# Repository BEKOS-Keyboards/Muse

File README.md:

# Muse
BOSS Keyboards Muse CAD and Design files

This is a full size "104" key keyboard that will run the QMK firmware, it has extra keys above the number row to allow for media control or other macros to be bound to the keys

Shield: [![CC BY-SA 4.0][cc-by-sa-shield]][cc-by-sa]

This work is licensed under a
[Creative Commons Attribution-ShareAlike 4.0 International License][cc-by-sa].

[![CC BY-SA 4.0][cc-by-sa-image]][cc-by-sa]

[cc-by-sa]: http://creativecommons.org/licenses/by-sa/4.0/
[cc-by-sa-image]: https://licensebuttons.net/l/by-sa/4.0/88x31.png
[cc-by-sa-shield]: https://img.shields.io/badge/License-CC%20BY--SA%204.0-lightgrey.svg

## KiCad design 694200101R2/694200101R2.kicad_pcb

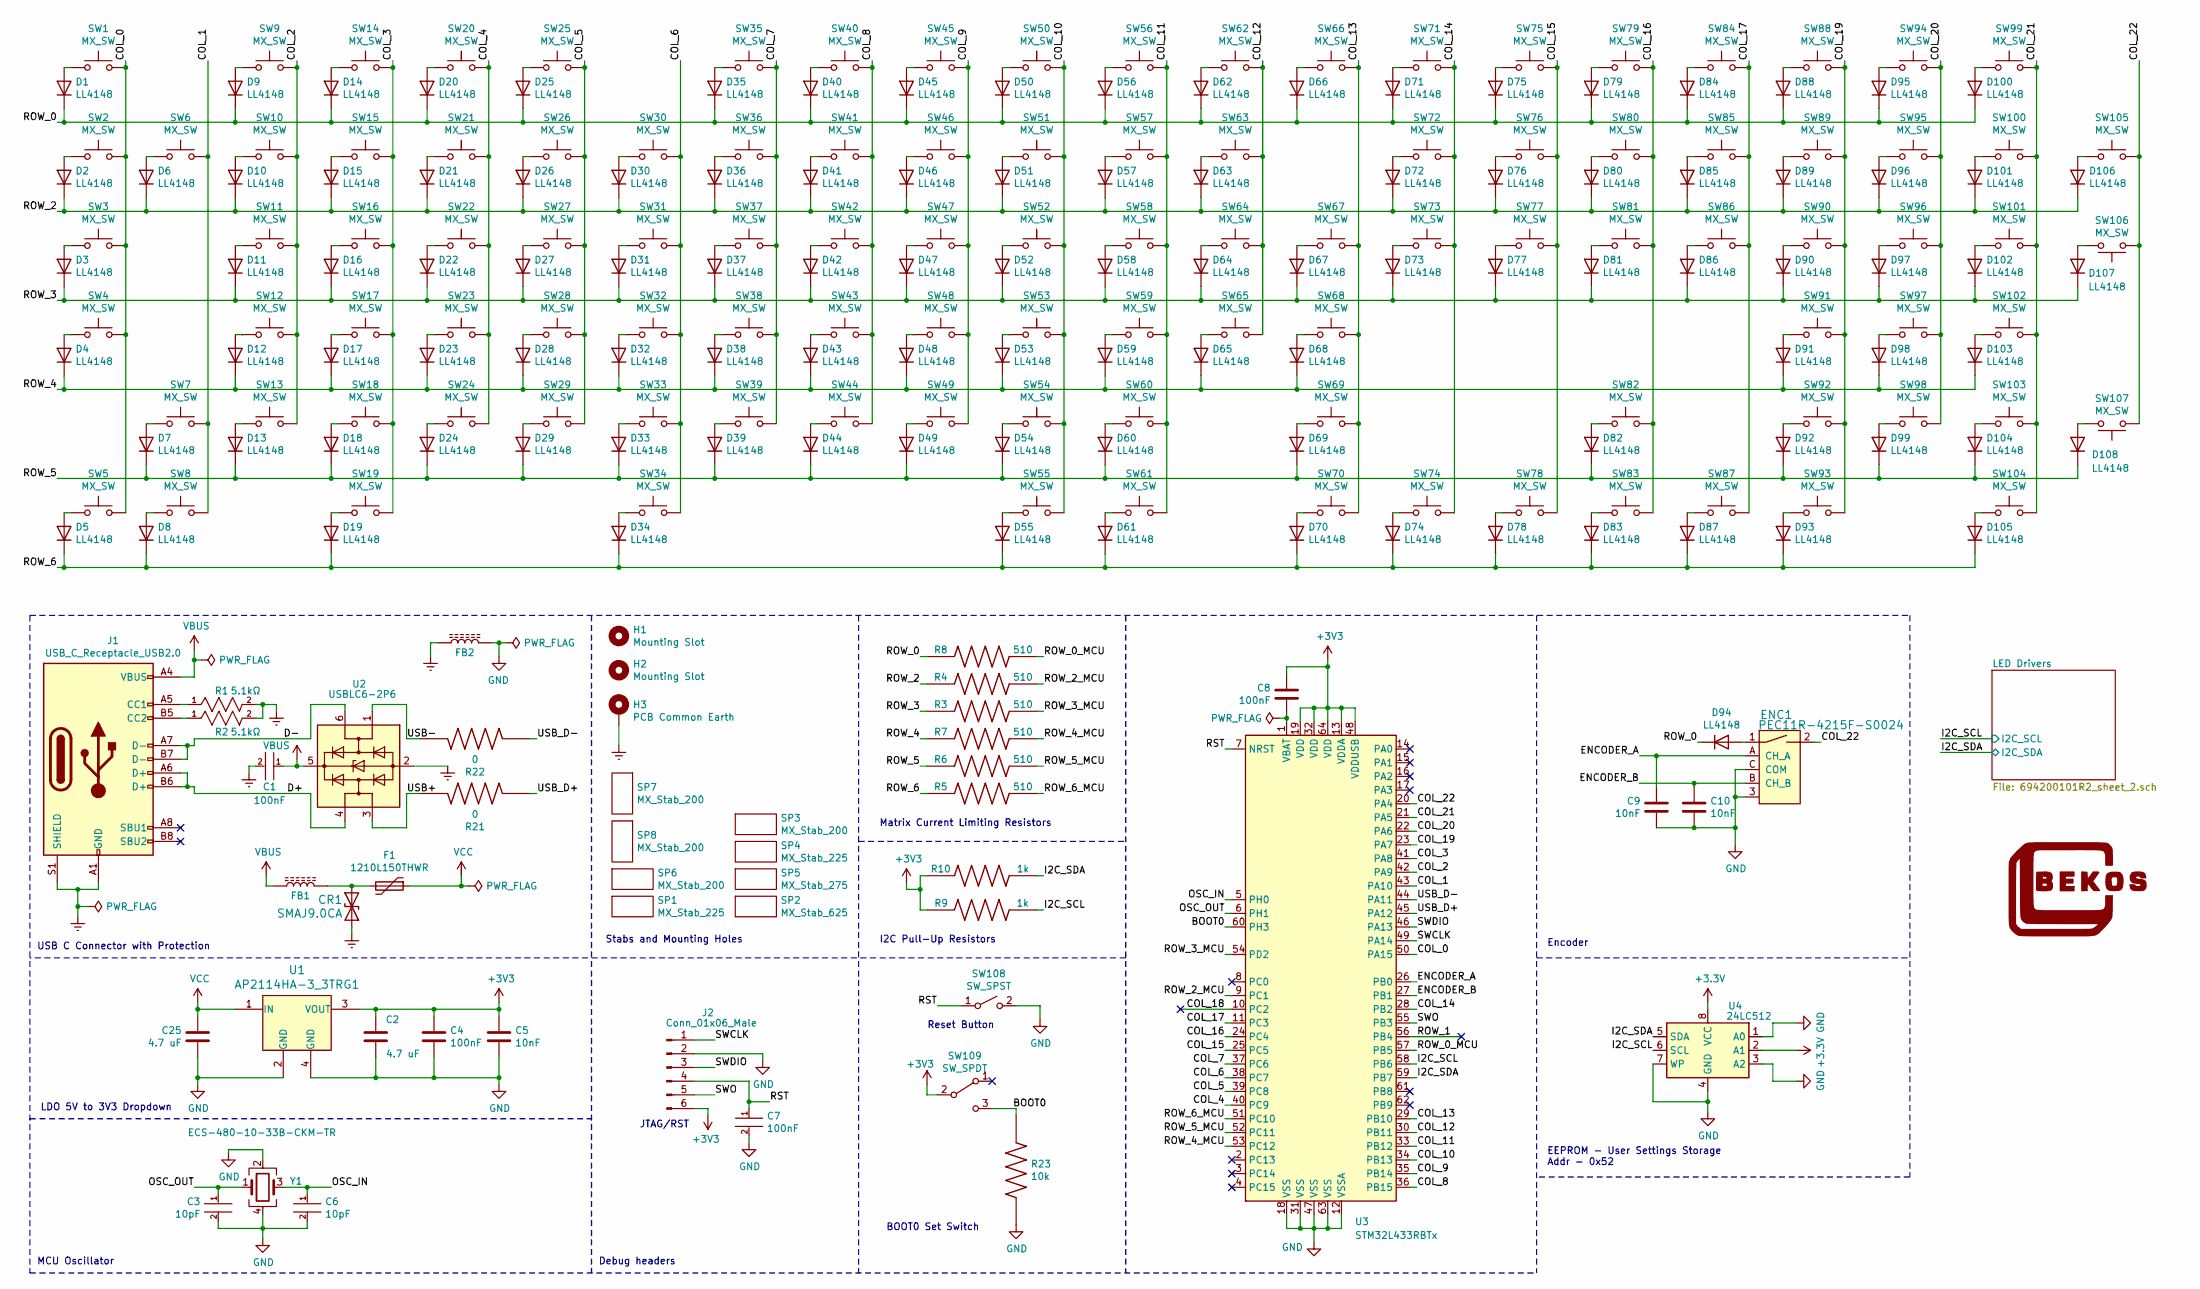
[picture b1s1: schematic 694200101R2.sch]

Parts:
C1, C7: CL10B104KB8NNNL; C_0603_1608Metric; tolerance 10%; voltage rating 50V
C2, C25: 4.7 uF; C_0805_2012Metric
C3, C6: 06035A100JAT2A; C_0603_1608Metric; tolerance 5%; voltage rating 50V; mouser part number 581-06035A100J; digikey description CAP CER 10PF 50V C0G/NP0 0603
C4, C8: 100nF; C_0603_1608Metric
C5, C9, C10: 10nF; C_0603_1608Metric
CR1: SMAJ9.0CA
D1, D9, D14, D20, D25, D35, D40, D45, D50, D56, D62, D66, D71, D75, D79: LL4148; D_MiniMELF
D2, D3, D4, D5, D6, D7, D8, D10, D11, D12, D13, D15, D16, D17, D18, D19, D21, D22, D23, D24, D26, D27, D28, D29, D30, D31, D32, D33, D34, D36, D37, D38, D39, D41, D42, D43, D44, D46, D47, D48, D49, D51, D52, D53, D54, D55, D57, D58, D59, D60, D61, D63, D64, D65, D67, D68, D69, D70, D72, D73, D74, D76, D77, D78, D80, D81, D82, D83, D84, D85, D86, D87, D88, D89, D90, D91, D92, D93, D94, D95, D96, D97, D98, D99, D100, D101, D102, D103, D104, D105, D106, D107, D108: LL4148; D_MiniMELF; mouser part number 512-LL4148; digikey description DIODE GEN PURP 100V 200MA SOD80
ENC1: PEC11R-4215F-S0024; Rotary_Encoder_Switched_PEC11R; MPN PEC11R-4215F-S0024; Digi-Key_PN PEC11R-4215F-S0024-ND
F1: 1210L150THWR; Fuse_1210_3225Metric_Castellated
FB1, FB2: FBMJ3216HM600-T; L_1206_3216Metric
H1, H2: Mounting Slot; MountingHole_M2_edge
H3: PCB Common Earth; MountingHole_3.5mm_Pad_TopBottom
J1: USB_C_Receptacle_USB2.0; USB_C_Receptacle_GCT_USB4085
J2: Conn_01x06_Male; PinHeader_1x06_P2.54mm_Vertical
R1, R2: RC0603FR-075K1L; R_0603_1608Metric; power rating 0.1W; tolerance 1%; mouser part number 603-RC0603FR-075K1L; digikey description RES SMD 5.1K OHM 1% 1/10W 0603
R3, R4, R5, R6, R7, R8: RMCF0805FT510R; R_0805_2012Metric
R9, R10: RMCF0603FT1K00; R_0603_1608Metric
R21, R22: MCT06030Z0000ZP500; R_0603_1608Metric
R23: RNCP0603FTD10K0; R_0603_1608Metric
SP1, SP4: MX_Stab_225; Mx_Stab_225
SP2: MX_Stab_625; Mx_Stab_625
SP3, SP6, SP7, SP8: MX_Stab_200; Mx_Stab_200
SP5: MX_Stab_275; Mx_Stab_275
SW1, SW2, SW3, SW4, SW5, SW6, SW7, SW8, SW9, SW10, SW11, SW12, SW13, SW14, SW15, SW16, SW17, SW18, SW19, SW20, SW21, SW22, SW23, SW24, SW25, SW26, SW27, SW28, SW29, SW30, SW31, SW32, SW33, SW34, SW35, SW36, SW37, SW38, SW39, SW40, SW41, SW42, SW43, SW44, SW45, SW46, SW47, SW48, SW49, SW50, SW51, SW52, SW53, SW54, SW55, SW56, SW57, SW58, SW59, SW60, SW61, SW62, SW63, SW64, SW65, SW66, SW67, SW68, SW69, SW70, SW71, SW72, SW73, SW74, SW75, SW76, SW77, SW78, SW79, SW80, SW81, SW82, SW83, SW84, SW85, SW86, SW87, SW88, SW89, SW90, SW91, SW92, SW93, SW94, SW95, SW96, SW97, SW98, SW99, SW100, SW101, SW102, SW103, SW104, SW105, SW106, SW107: MX_SW; millmax-mxalps
SW108: SW_SPST; SW_SPST_TL3342
SW109: SW_SPDT; SW_SPDT_PCM12
U1: AP2114HA-3_3TRG1; SOT-223; MPN AP2114H-3.3TRG1; Digi-Key_PN AP2114H-3.3TRG1DICT-ND
U2: USBLC6-2P6; SOT-666
U3: STM32L433RBTx; LQFP-64_10x10mm_P0.5mm
U4: 24LC512; SOIC-8_3.9x4.9mm_P1.27mm
Y1: ECS-480-10-33B-CKM-TR; XTAL_ECS-480-10-33B-CKM-TR

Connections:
/BOOT0: R23.1, SW109.3 (C), U3.60 (PH3)
/COL_0: SW1.2, SW2.2, SW3.2, SW4.2, SW5.2, U3.50 (PA15)
/COL_1: SW6.2, SW7.2, SW8.2, U3.43 (PA10)
/COL_2: SW9.2, SW10.2, SW11.2, SW12.2, SW13.2, U3.42 (PA9)
/COL_3: SW14.2, SW15.2, SW16.2, SW17.2, SW18.2, SW19.2, U3.41 (PA8)
/COL_4: SW20.2, SW21.2, SW22.2, SW23.2, SW24.2, U3.40 (PC9)
/COL_5: SW25.2, SW26.2, SW27.2, SW28.2, SW29.2, U3.39 (PC8)
/COL_6: SW30.2, SW31.2, SW32.2, SW33.2, SW34.2, U3.38 (PC7)
/COL_7: SW35.2, SW36.2, SW37.2, SW38.2, SW39.2, U3.37 (PC6)
/COL_8: SW40.2, SW41.2, SW42.2, SW43.2, SW44.2, U3.36 (PB15)
/COL_9: SW45.2, SW46.2, SW47.2, SW48.2, SW49.2, U3.35 (PB14)
/COL_10: SW50.2, SW51.2, SW52.2, SW53.2, SW54.2, SW55.2, U3.34 (PB13)
/COL_11: SW56.2, SW57.2, SW58.2, SW59.2, SW60.2, SW61.2, U3.33 (PB12)
/COL_12: SW62.2, SW63.2, SW64.2, SW65.2, U3.30 (PB11)
/COL_13: SW66.2, SW67.2, SW68.2, SW69.2, SW70.2, U3.29 (PB10)
/COL_14: SW71.2, SW72.2, SW73.2, SW74.2, U3.28 (PB2)
/COL_15: SW75.2, SW76.2, SW77.2, SW78.2, U3.25 (PC5)
/COL_16: SW79.2, SW80.2, SW81.2, SW82.2, SW83.2, U3.24 (PC4)
/COL_17: SW84.2, SW85.2, SW86.2, SW87.2, U3.11 (PC3)
/COL_18: U3.10 (PC2)
/COL_19: SW88.2, SW89.2, SW90.2, SW91.2, SW92.2, SW93.2, U3.23 (PA7)
/COL_20: SW94.2, SW95.2, SW96.2, SW97.2, SW98.2, U3.22 (PA6)
/COL_21: SW99.2, SW100.2, SW101.2, SW102.2, SW103.2, SW104.2, U3.21 (PA5)
/COL_22: ENC1.2, SW105.2, SW106.1, SW107.1, U3.20 (PA4)
/D+: J1.A6 (D+), J1.B6 (D+), U2.4 (I/O2)
/D-: J1.A7 (D-), J1.B7 (D-), U2.6 (I/O1)
/ENCODER_A: C9.1, ENC1.A (CH_A), U3.26 (PB0)
/ENCODER_B: C10.1, ENC1.B (CH_B), U3.27 (PB1)
/I2C_SCL: R9.2, U3.58 (PB6), U4.6 (SCL); also elsewhere on the board
/I2C_SDA: R10.2, U3.59 (PB7), U4.5 (SDA); also elsewhere on the board
/OSC_IN: C6.1, U3.5 (PH0), Y1.3
/OSC_OUT: C3.1, U3.6 (PH1), Y1.1
/ROW_0: D1.1 (K), D9.1 (K), D14.1 (K), D20.1 (K), D25.1 (K), D35.1 (K), D40.1 (K), D45.1 (K), D50.1 (K), D56.1 (K), D62.1 (K), D66.1 (K), D71.1 (K), D75.1 (K), D79.1 (K), D84.1 (K), D88.1 (K), D94.1 (K), D95.1 (K), D100.1 (K), R8.2
/ROW_0_MCU: R8.1, U3.57 (PB5)
/ROW_1: U3.56 (PB4)
/ROW_2: D2.1 (K), D6.1 (K), D10.1 (K), D15.1 (K), D21.1 (K), D26.1 (K), D30.1 (K), D36.1 (K), D41.1 (K), D46.1 (K), D51.1 (K), D57.1 (K), D63.1 (K), D72.1 (K), D76.1 (K), D80.1 (K), D85.1 (K), D89.1 (K), D96.1 (K), D101.1 (K), D106.1 (K), R4.1
/ROW_2_MCU: R4.2, U3.9 (PC1)
/ROW_3: D3.1 (K), D11.1 (K), D16.1 (K), D22.1 (K), D27.1 (K), D31.1 (K), D37.1 (K), D42.1 (K), D47.1 (K), D52.1 (K), D58.1 (K), D64.1 (K), D67.1 (K), D73.1 (K), D77.1 (K), D81.1 (K), D86.1 (K), D90.1 (K), D97.1 (K), D102.1 (K), D107.1 (K), R3.1
/ROW_3_MCU: R3.2, U3.54 (PD2)
/ROW_4: D4.1 (K), D12.1 (K), D17.1 (K), D23.1 (K), D28.1 (K), D32.1 (K), D38.1 (K), D43.1 (K), D48.1 (K), D53.1 (K), D59.1 (K), D65.1 (K), D68.1 (K), D91.1 (K), D98.1 (K), D103.1 (K), R7.1
/ROW_4_MCU: R7.2, U3.53 (PC12)
/ROW_5: D7.1 (K), D13.1 (K), D18.1 (K), D24.1 (K), D29.1 (K), D33.1 (K), D39.1 (K), D44.1 (K), D49.1 (K), D54.1 (K), D60.1 (K), D69.1 (K), D82.1 (K), D92.1 (K), D99.1 (K), D104.1 (K), D108.1 (K), R6.1
/ROW_5_MCU: R6.2, U3.52 (PC11)
/ROW_6: D5.1 (K), D8.1 (K), D19.1 (K), D34.1 (K), D55.1 (K), D61.1 (K), D70.1 (K), D74.1 (K), D78.1 (K), D83.1 (K), D87.1 (K), D93.1 (K), D105.1 (K), R5.1
/ROW_6_MCU: R5.2, U3.51 (PC10)
/RST: C7.1, J2.4, SW108.1 (A), U3.7 (NRST)
/SWCLK: J2.1, U3.49 (PA14)
/SWDIO: J2.3, U3.46 (PA13)
/SWO: J2.5, U3.55 (PB3)
/USB+: R21.1, U2.3 (I/O2)
/USB-: R22.1, U2.1 (I/O1)
/USB_D+: R21.2, U3.45 (PA12)
/USB_D-: R22.2, U3.44 (PA11)
Earth: C1.2, CR1.2 (A2), FB2.1, H3.1, J1.A1 (GND), J1.A12 (GND), J1.B1 (GND), J1.B12 (GND), J1.S1 (SHIELD), R1.2, R2.2, U2.2 (GND)
GND: C2.2, C3.2, C4.2, C5.2, C6.2, C7.2, C9.2, C10.2, C25.2, ENC1.3, ENC1.C (COM), FB2.2, J2.2, R23.2, SW108.2 (B), U1.2 (GND), U1.4 (GND), U3.12 (VSSA), U3.18 (VSS), U3.31 (VSS), U3.47 (VSS), U3.63 (VSS), U4.1 (A0), U4.3 (A2), U4.4 (GND), U4.7 (WP), Y1.2, Y1.4; also elsewhere on the board
unnamed: C8.2, U3.1 (VBAT)
unnamed: CR1.1 (A1), F1.2, FB1.1
unnamed: D1.2 (A), SW1.1
unnamed: D2.2 (A), SW2.1
unnamed: D3.2 (A), SW3.1
unnamed: D4.2 (A), SW4.1
unnamed: D5.2 (A), SW5.1
unnamed: D6.2 (A), SW6.1
unnamed: D7.2 (A), SW7.1
unnamed: D8.2 (A), SW8.1
unnamed: D9.2 (A), SW9.1
unnamed: D10.2 (A), SW10.1
unnamed: D11.2 (A), SW11.1
unnamed: D12.2 (A), SW12.1
unnamed: D13.2 (A), SW13.1
unnamed: D14.2 (A), SW14.1
unnamed: D15.2 (A), SW15.1
unnamed: D16.2 (A), SW16.1
unnamed: D17.2 (A), SW17.1
unnamed: D18.2 (A), SW18.1
unnamed: D19.2 (A), SW19.1
unnamed: D20.2 (A), SW20.1
unnamed: D21.2 (A), SW21.1
unnamed: D22.2 (A), SW22.1
unnamed: D23.2 (A), SW23.1
unnamed: D24.2 (A), SW24.1
unnamed: D25.2 (A), SW25.1
unnamed: D26.2 (A), SW26.1
unnamed: D27.2 (A), SW27.1
unnamed: D28.2 (A), SW28.1
unnamed: D29.2 (A), SW29.1
unnamed: D30.2 (A), SW30.1
unnamed: D31.2 (A), SW31.1
unnamed: D32.2 (A), SW32.1
unnamed: D33.2 (A), SW33.1
unnamed: D34.2 (A), SW34.1
unnamed: D35.2 (A), SW35.1
unnamed: D36.2 (A), SW36.1
unnamed: D37.2 (A), SW37.1
unnamed: D38.2 (A), SW38.1
unnamed: D39.2 (A), SW39.1
unnamed: D40.2 (A), SW40.1
unnamed: D41.2 (A), SW41.1
unnamed: D42.2 (A), SW42.1
unnamed: D43.2 (A), SW43.1
unnamed: D44.2 (A), SW44.1
unnamed: D45.2 (A), SW45.1
unnamed: D46.2 (A), SW46.1
unnamed: D47.2 (A), SW47.1
unnamed: D48.2 (A), SW48.1
unnamed: D49.2 (A), SW49.1
unnamed: D50.2 (A), SW50.1
unnamed: D51.2 (A), SW51.1
unnamed: D52.2 (A), SW52.1
unnamed: D53.2 (A), SW53.1
unnamed: D54.2 (A), SW54.1
unnamed: D55.2 (A), SW55.1
unnamed: D56.2 (A), SW56.1
unnamed: D57.2 (A), SW57.1
unnamed: D58.2 (A), SW58.1
unnamed: D59.2 (A), SW59.1
unnamed: D60.2 (A), SW60.1
unnamed: D61.2 (A), SW61.1
unnamed: D62.2 (A), SW62.1
unnamed: D63.2 (A), SW63.1
unnamed: D64.2 (A), SW64.1
unnamed: D65.2 (A), SW65.1
unnamed: D66.2 (A), SW66.1
unnamed: D67.2 (A), SW67.1
unnamed: D68.2 (A), SW68.1
unnamed: D69.2 (A), SW69.1
unnamed: D70.2 (A), SW70.1
unnamed: D71.2 (A), SW71.1
unnamed: D72.2 (A), SW72.1
unnamed: D73.2 (A), SW73.1
unnamed: D74.2 (A), SW74.1
unnamed: D75.2 (A), SW75.1
unnamed: D76.2 (A), SW76.1
unnamed: D77.2 (A), SW77.1
unnamed: D78.2 (A), SW78.1
unnamed: D79.2 (A), SW79.1
unnamed: D80.2 (A), SW80.1
unnamed: D81.2 (A), SW81.1
unnamed: D82.2 (A), SW82.1
unnamed: D83.2 (A), SW83.1
unnamed: D84.2 (A), SW84.1
unnamed: D85.2 (A), SW85.1
unnamed: D86.2 (A), SW86.1
unnamed: D87.2 (A), SW87.1
unnamed: D88.2 (A), SW88.1
unnamed: D89.2 (A), SW89.1
unnamed: D90.2 (A), SW90.1
unnamed: D91.2 (A), SW91.1
unnamed: D92.2 (A), SW92.1
unnamed: D93.2 (A), SW93.1
unnamed: D94.2 (A), ENC1.1
unnamed: D95.2 (A), SW94.1
unnamed: D96.2 (A), SW95.1
unnamed: D97.2 (A), SW96.1
unnamed: D98.2 (A), SW97.1
unnamed: D99.2 (A), SW98.1
unnamed: D100.2 (A), SW99.1
unnamed: D101.2 (A), SW100.1
unnamed: D102.2 (A), SW101.1
unnamed: D103.2 (A), SW102.1
unnamed: D104.2 (A), SW103.1
unnamed: D105.2 (A), SW104.1
unnamed: D106.2 (A), SW105.1
unnamed: D107.2 (A), SW106.2
unnamed: D108.2 (A), SW107.2
unnamed: J1.A5 (CC1), R1.1
unnamed: J1.B5 (CC2), R2.1
VBUS: C1.1, FB1.2, J1.A4 (VBUS), J1.A9 (VBUS), J1.B4 (VBUS), J1.B9 (VBUS), U2.5 (VBUS)
VCC: C25.1, F1.1, U1.1 (IN); also elsewhere on the board

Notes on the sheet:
USB C Connector with Protection
LDO 5V to 3V3 Dropdown
MCU Oscillator
JTAG/RST
Stabs and Mounting Holes
Matrix Current Limiting Resistors
I2C Pull-Up Resistors
Encoder
Debug headers
BOOT0 Set Switch
Reset Button
EEPROM - User Settings Storage Addr - 0x52

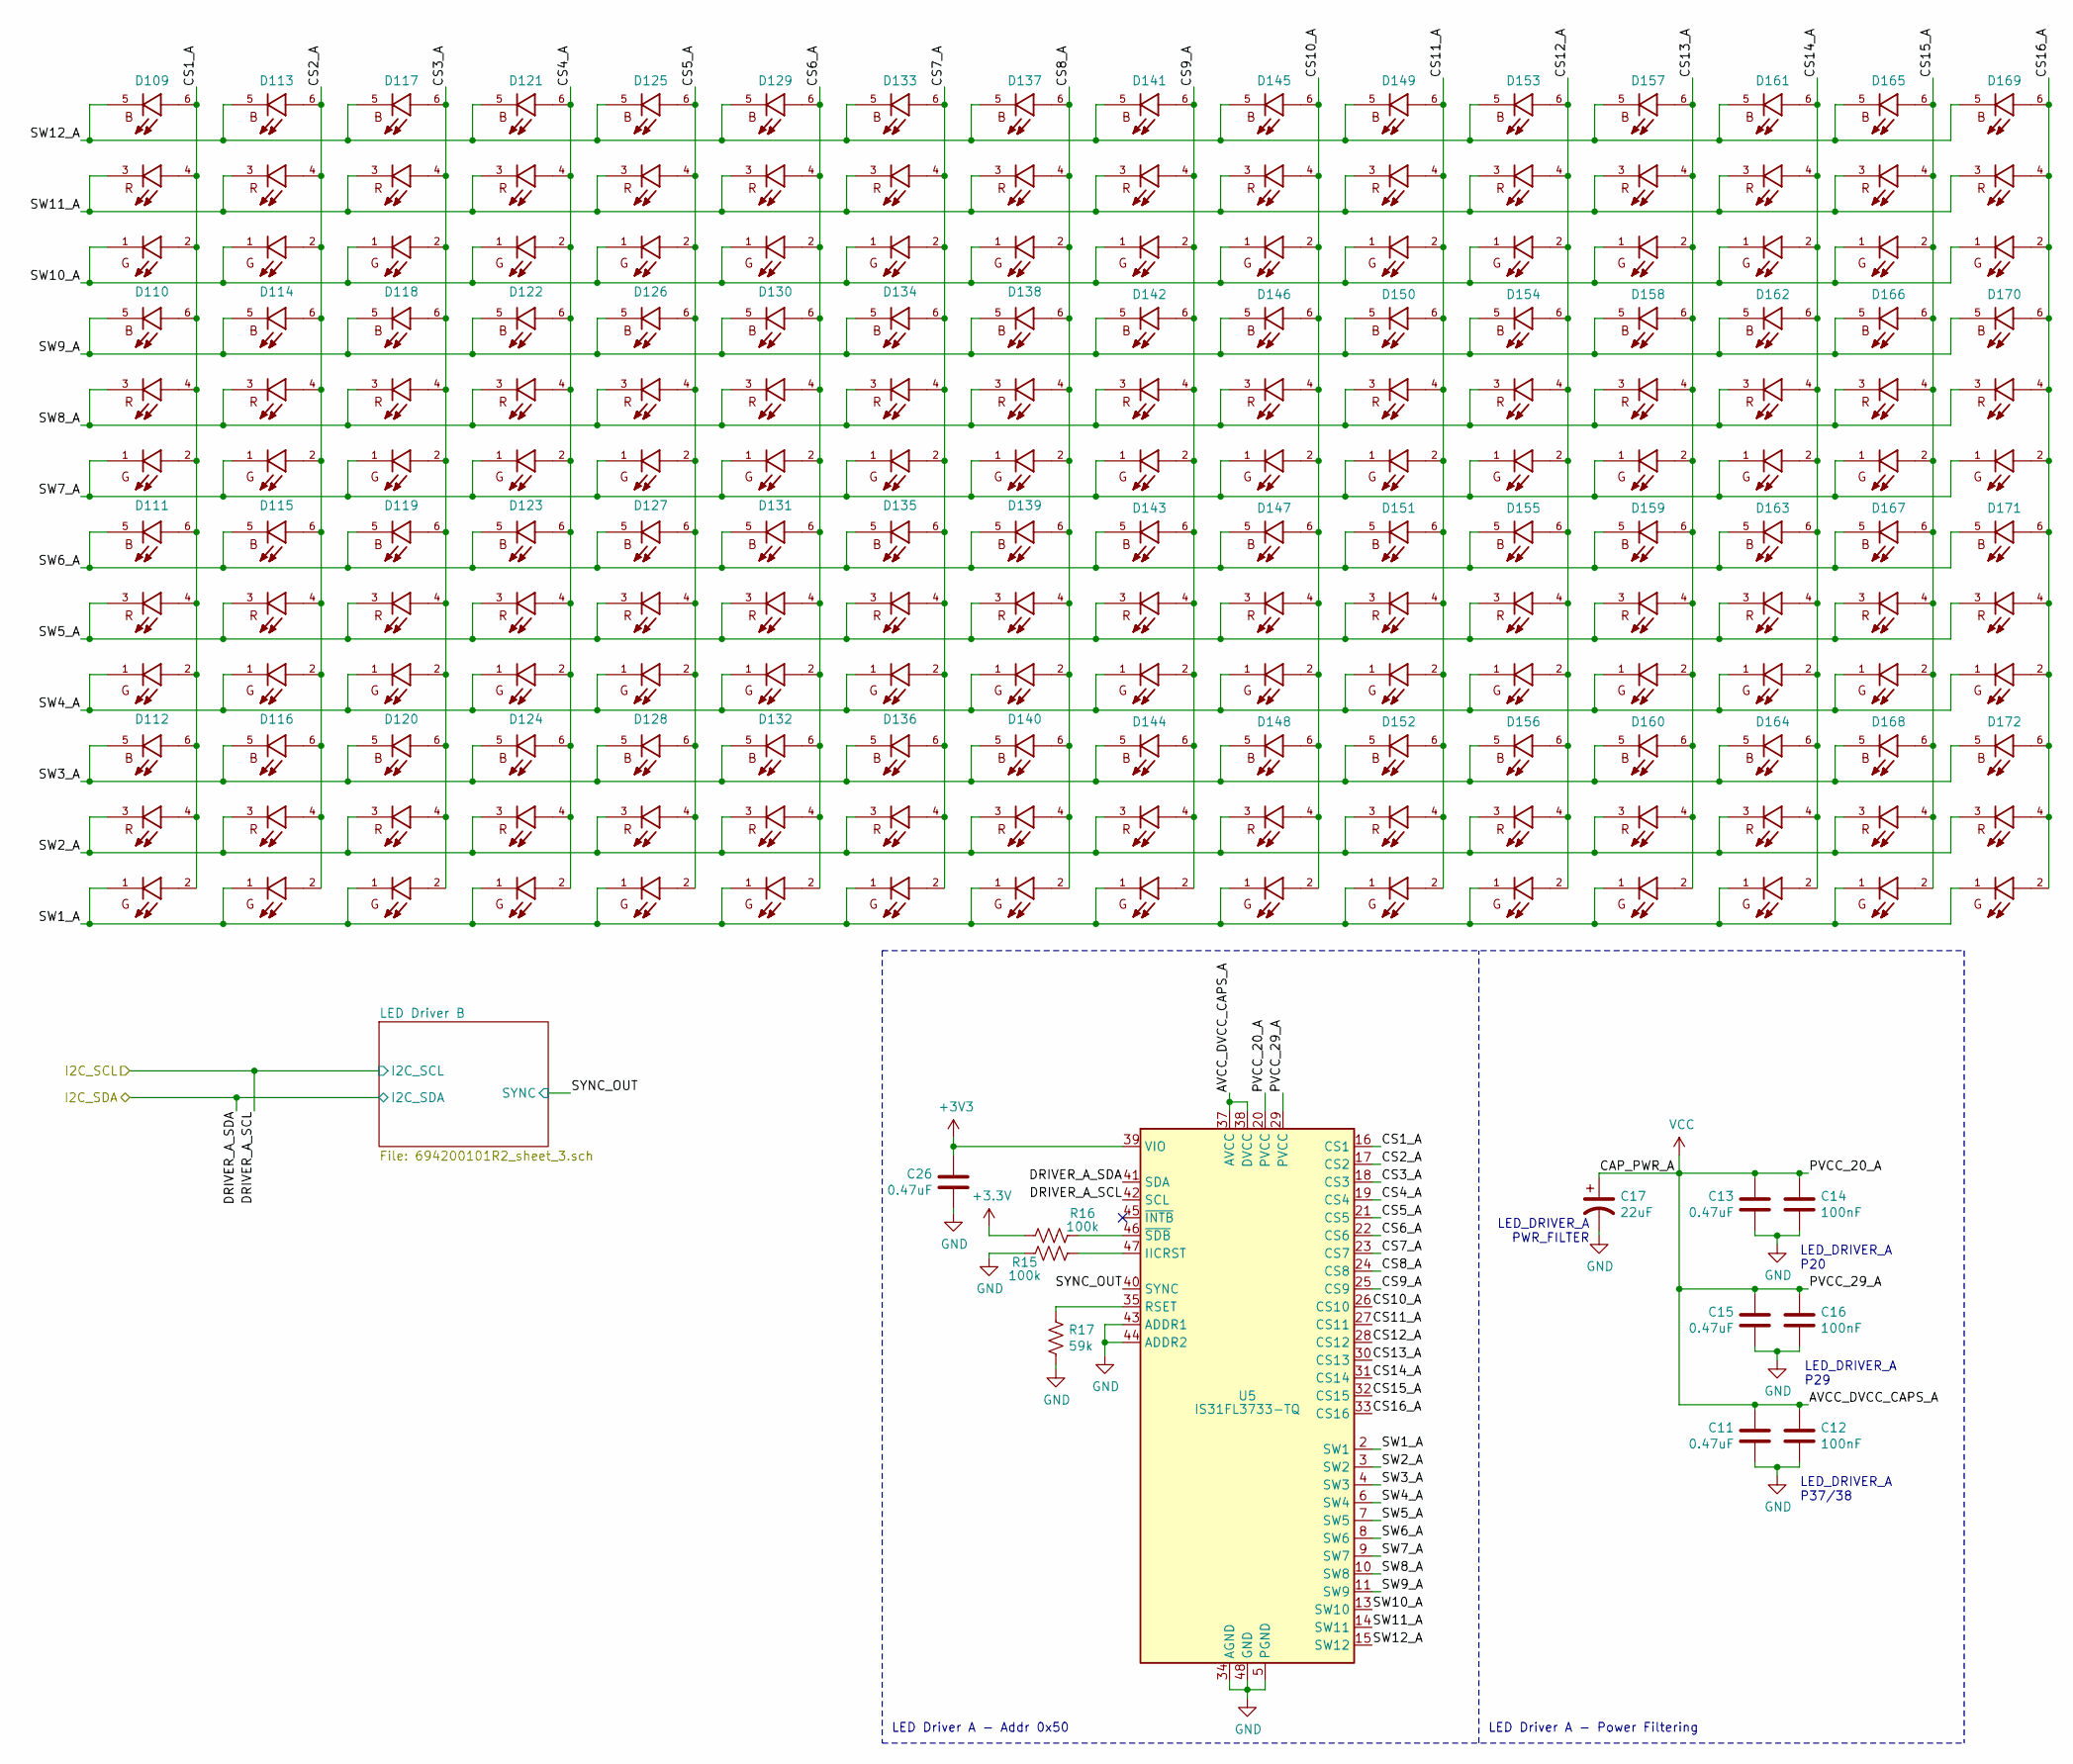
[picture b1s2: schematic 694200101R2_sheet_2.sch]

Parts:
C11, C13, C15, C26: 0.47uF; C_0603_1608Metric
C12, C14, C16: 100nF; C_0603_1608Metric
C17: 22uF; CP_EIA-3528-21_Kemet-B
D109, D110, D111, D112, D113, D114, D115, D116, D117, D118, D119, D120, D121, D122, D123, D124, D125, D126, D127, D128, D129, D130, D131, D132, D133, D134, D135, D136, D137, D138, D139, D140, D141, D142, D143, D144, D145, D146, D147, D148, D149, D150, D151, D152, D153, D154, D155, D156, D157, D158, D159, D160, D161, D162, D163, D164, D165, D166, D167, D168, D169, D170, D171, D172: 19-337C_RSBHGHC-A88_4T; 4T; PARTREV 2
R15, R16: 100k; R_0603_1608Metric
R17: 59k; R_2512_6332Metric
U5: IS31FL3733-TQ; TQFP-48-1EP_7x7mm_P0.5mm_EP5x5mm_ThermalVias

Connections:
/I2C_SCL: U5.42 (SCL); also elsewhere on the board
/I2C_SDA: U5.41 (SDA); also elsewhere on the board
/LED Drivers/CS1_A: D109.2, D109.4, D109.6, D110.2, D110.4, D110.6, D111.2, D111.4, D111.6, D112.2, D112.4, D112.6, U5.16 (CS1)
/LED Drivers/CS2_A: D113.2, D113.4, D113.6, D114.2, D114.4, D114.6, D115.2, D115.4, D115.6, D116.2, D116.4, D116.6, U5.17 (CS2)
/LED Drivers/CS3_A: D117.2, D117.4, D117.6, D118.2, D118.4, D118.6, D119.2, D119.4, D119.6, D120.2, D120.4, D120.6, U5.18 (CS3)
/LED Drivers/CS4_A: D121.2, D121.4, D121.6, D122.2, D122.4, D122.6, D123.2, D123.4, D123.6, D124.2, D124.4, D124.6, U5.19 (CS4)
/LED Drivers/CS5_A: D125.2, D125.4, D125.6, D126.2, D126.4, D126.6, D127.2, D127.4, D127.6, D128.2, D128.4, D128.6, U5.21 (CS5)
/LED Drivers/CS6_A: D129.2, D129.4, D129.6, D130.2, D130.4, D130.6, D131.2, D131.4, D131.6, D132.2, D132.4, D132.6, U5.22 (CS6)
/LED Drivers/CS7_A: D133.2, D133.4, D133.6, D134.2, D134.4, D134.6, D135.2, D135.4, D135.6, D136.2, D136.4, D136.6, U5.23 (CS7)
/LED Drivers/CS8_A: D137.2, D137.4, D137.6, D138.2, D138.4, D138.6, D139.2, D139.4, D139.6, D140.2, D140.4, D140.6, U5.24 (CS8)
/LED Drivers/CS9_A: D141.2, D141.4, D141.6, D142.2, D142.4, D142.6, D143.2, D143.4, D143.6, D144.2, D144.4, D144.6, U5.25 (CS9)
/LED Drivers/CS10_A: D145.2, D145.4, D145.6, D146.2, D146.4, D146.6, D147.2, D147.4, D147.6, D148.2, D148.4, D148.6, U5.26 (CS10)
/LED Drivers/CS11_A: D149.2, D149.4, D149.6, D150.2, D150.4, D150.6, D151.2, D151.4, D151.6, D152.2, D152.4, D152.6, U5.27 (CS11)
/LED Drivers/CS12_A: D153.2, D153.4, D153.6, D154.2, D154.4, D154.6, D155.2, D155.4, D155.6, D156.2, D156.4, D156.6, U5.28 (CS12)
/LED Drivers/CS13_A: D157.2, D157.4, D157.6, D158.2, D158.4, D158.6, D159.2, D159.4, D159.6, D160.2, D160.4, D160.6, U5.30 (CS13)
/LED Drivers/CS14_A: D161.2, D161.4, D161.6, D162.2, D162.4, D162.6, D163.2, D163.4, D163.6, D164.2, D164.4, D164.6, U5.31 (CS14)
/LED Drivers/CS15_A: D165.2, D165.4, D165.6, D166.2, D166.4, D166.6, D167.2, D167.4, D167.6, D168.2, D168.4, D168.6, U5.32 (CS15)
/LED Drivers/CS16_A: D169.2, D169.4, D169.6, D170.2, D170.4, D170.6, D171.2, D171.4, D171.6, D172.2, D172.4, D172.6, U5.33 (CS16)
/LED Drivers/SW1_A: D112.1, D116.1, D120.1, D124.1, D128.1, D132.1, D136.1, D140.1, D144.1, D148.1, D152.1, D156.1, D160.1, D164.1, D168.1, D172.1, U5.2 (SW1)
/LED Drivers/SW2_A: D112.3, D116.3, D120.3, D124.3, D128.3, D132.3, D136.3, D140.3, D144.3, D148.3, D152.3, D156.3, D160.3, D164.3, D168.3, D172.3, U5.3 (SW2)
/LED Drivers/SW3_A: D112.5, D116.5, D120.5, D124.5, D128.5, D132.5, D136.5, D140.5, D144.5, D148.5, D152.5, D156.5, D160.5, D164.5, D168.5, D172.5, U5.4 (SW3)
/LED Drivers/SW4_A: D111.1, D115.1, D119.1, D123.1, D127.1, D131.1, D135.1, D139.1, D143.1, D147.1, D151.1, D155.1, D159.1, D163.1, D167.1, D171.1, U5.6 (SW4)
/LED Drivers/SW5_A: D111.3, D115.3, D119.3, D123.3, D127.3, D131.3, D135.3, D139.3, D143.3, D147.3, D151.3, D155.3, D159.3, D163.3, D167.3, D171.3, U5.7 (SW5)
/LED Drivers/SW6_A: D111.5, D115.5, D119.5, D123.5, D127.5, D131.5, D135.5, D139.5, D143.5, D147.5, D151.5, D155.5, D159.5, D163.5, D167.5, D171.5, U5.8 (SW6)
/LED Drivers/SW7_A: D110.1, D114.1, D118.1, D122.1, D126.1, D130.1, D134.1, D138.1, D142.1, D146.1, D150.1, D154.1, D158.1, D162.1, D166.1, D170.1, U5.9 (SW7)
/LED Drivers/SW8_A: D110.3, D114.3, D118.3, D122.3, D126.3, D130.3, D134.3, D138.3, D142.3, D146.3, D150.3, D154.3, D158.3, D162.3, D166.3, D170.3, U5.10 (SW8)
/LED Drivers/SW9_A: D110.5, D114.5, D118.5, D122.5, D126.5, D130.5, D134.5, D138.5, D142.5, D146.5, D150.5, D154.5, D158.5, D162.5, D166.5, D170.5, U5.11 (SW9)
/LED Drivers/SW10_A: D109.1, D113.1, D117.1, D121.1, D125.1, D129.1, D133.1, D137.1, D141.1, D145.1, D149.1, D153.1, D157.1, D161.1, D165.1, D169.1, U5.13 (SW10)
/LED Drivers/SW11_A: D109.3, D113.3, D117.3, D121.3, D125.3, D129.3, D133.3, D137.3, D141.3, D145.3, D149.3, D153.3, D157.3, D161.3, D165.3, D169.3, U5.14 (SW11)
/LED Drivers/SW12_A: D109.5, D113.5, D117.5, D121.5, D125.5, D129.5, D133.5, D137.5, D141.5, D145.5, D149.5, D153.5, D157.5, D161.5, D165.5, D169.5, U5.15 (SW12)
/LED Drivers/SYNC_OUT: U5.40 (SYNC); also elsewhere on the board
GND: C11.2, C12.2, C13.2, C14.2, C15.2, C16.2, C17.2, C26.2, R15.1, R17.2, U5.5 (PGND), U5.12 (PGND), U5.34 (AGND), U5.43 (ADDR1), U5.44 (ADDR2), U5.48 (GND), U5.49 (GND); also elsewhere on the board
unnamed: R15.2, U5.47 (IICRST)
unnamed: R16.1, U5.46 (~SDB)
unnamed: R17.1, U5.35 (RSET)
VCC: C11.1, C12.1, C13.1, C14.1, C15.1, C16.1, C17.1, U5.20 (PVCC), U5.29 (PVCC), U5.37 (AVCC), U5.38 (DVCC); also elsewhere on the board

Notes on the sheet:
LED_DRIVER_A PWR_FILTER
LED_DRIVER_A P29
LED_DRIVER_A P20
LED_DRIVER_A P37/38
LED Driver A - Addr 0x50
LED Driver A - Power Filtering

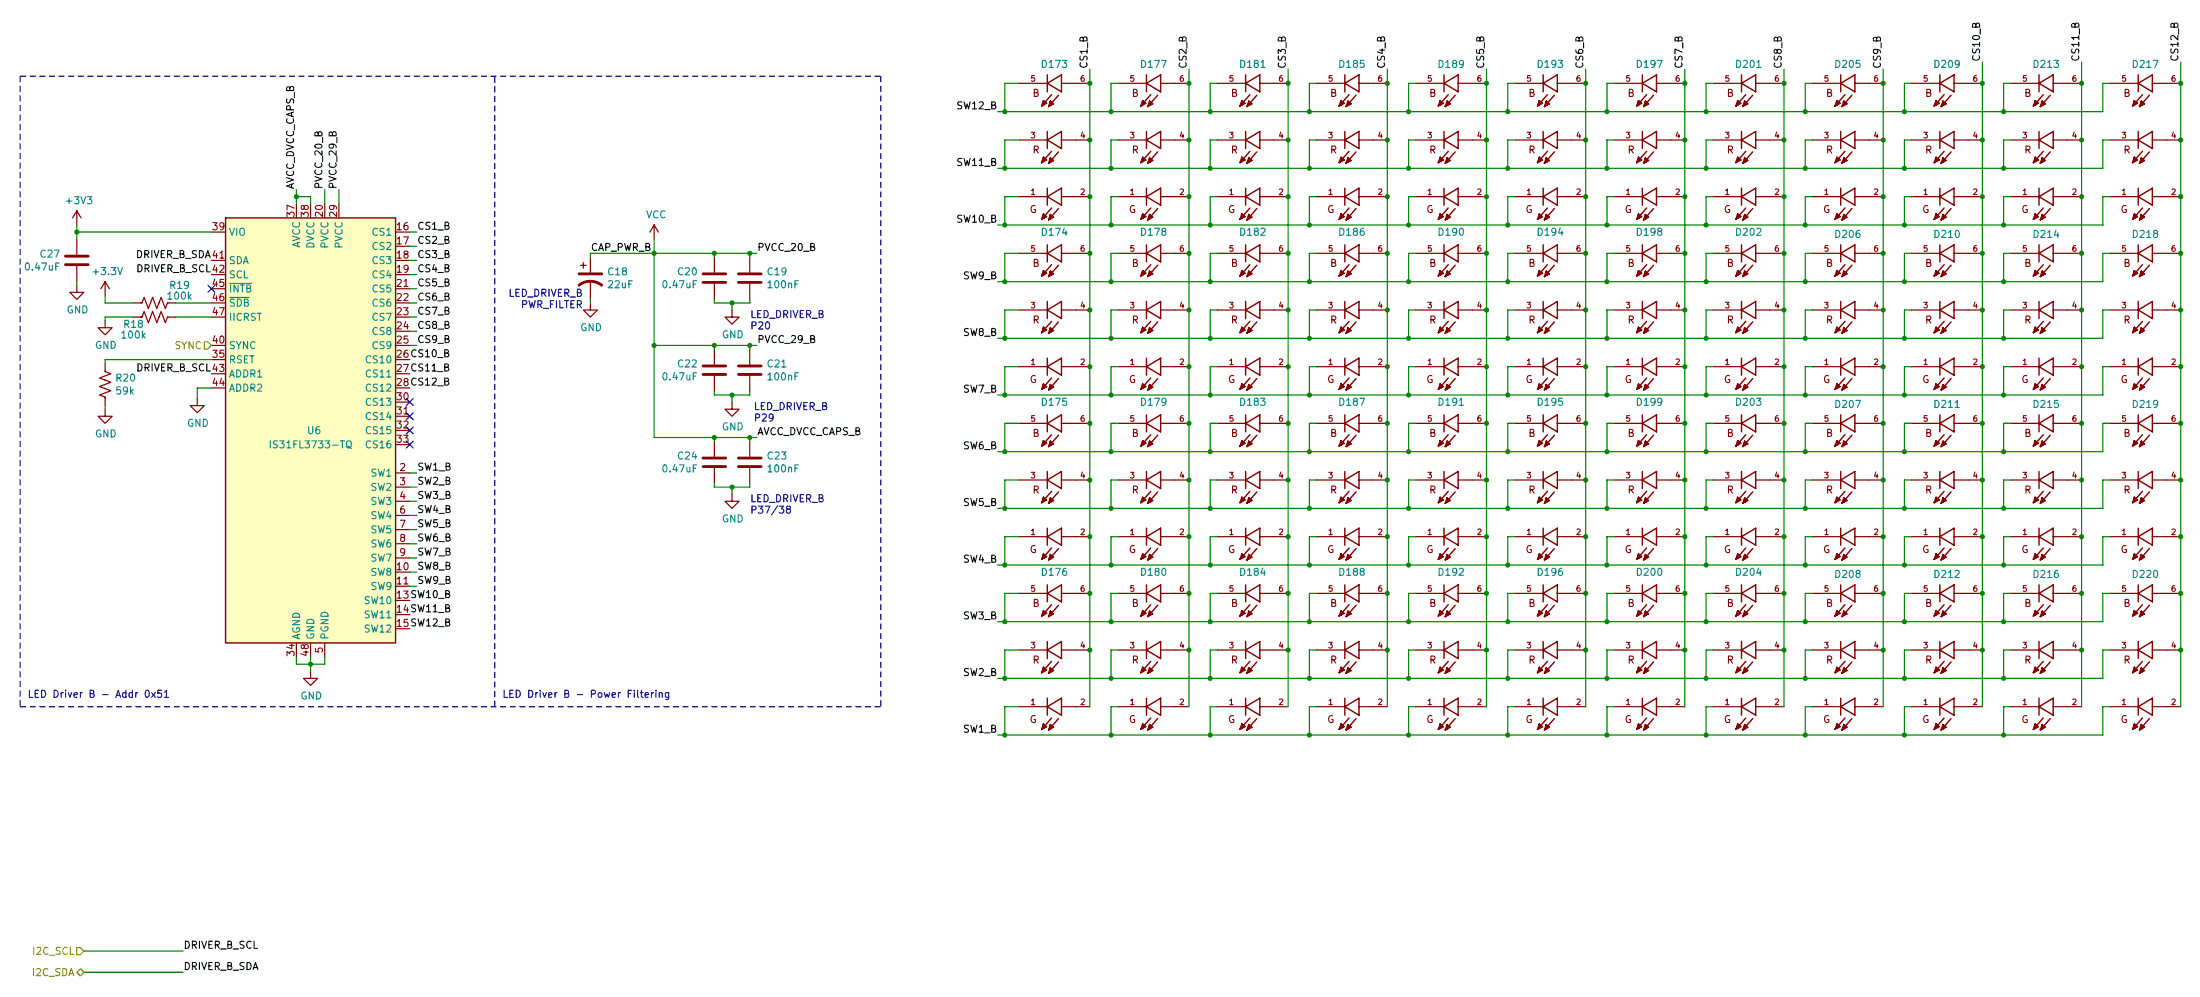
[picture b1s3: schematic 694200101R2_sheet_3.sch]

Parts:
C18: 22uF; CP_EIA-3528-21_Kemet-B
C19, C21, C23: 100nF; C_0603_1608Metric
C20, C22, C24, C27: 0.47uF; C_0603_1608Metric
D173, D174, D175, D176, D177, D178, D179, D180, D181, D182, D183, D184, D185, D186, D187, D188, D189, D190, D191, D192, D193, D194, D195, D196, D197, D198, D199, D200, D201, D202, D203, D204, D205, D206, D207, D208, D209, D210, D211, D212, D213, D214, D215, D216, D217, D218, D219, D220: 19-337C_RSBHGHC-A88_4T; 4T; PARTREV 2
R18, R19: 100k; R_0603_1608Metric
R20: 59k; R_2512_6332Metric
U6: IS31FL3733-TQ; TQFP-48-1EP_7x7mm_P0.5mm_EP5x5mm_ThermalVias

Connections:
/I2C_SCL: U6.42 (SCL), U6.43 (ADDR1); also elsewhere on the board
/I2C_SDA: U6.41 (SDA); also elsewhere on the board
/LED Drivers/LED Driver B/CS1_B: D173.2, D173.4, D173.6, D174.2, D174.4, D174.6, D175.2, D175.4, D175.6, D176.2, D176.4, D176.6, U6.16 (CS1)
/LED Drivers/LED Driver B/CS2_B: D177.2, D177.4, D177.6, D178.2, D178.4, D178.6, D179.2, D179.4, D179.6, D180.2, D180.4, D180.6, U6.17 (CS2)
/LED Drivers/LED Driver B/CS3_B: D181.2, D181.4, D181.6, D182.2, D182.4, D182.6, D183.2, D183.4, D183.6, D184.2, D184.4, D184.6, U6.18 (CS3)
/LED Drivers/LED Driver B/CS4_B: D185.2, D185.4, D185.6, D186.2, D186.4, D186.6, D187.2, D187.4, D187.6, D188.2, D188.4, D188.6, U6.19 (CS4)
/LED Drivers/LED Driver B/CS5_B: D189.2, D189.4, D189.6, D190.2, D190.4, D190.6, D191.2, D191.4, D191.6, D192.2, D192.4, D192.6, U6.21 (CS5)
/LED Drivers/LED Driver B/CS6_B: D193.2, D193.4, D193.6, D194.2, D194.4, D194.6, D195.2, D195.4, D195.6, D196.2, D196.4, D196.6, U6.22 (CS6)
/LED Drivers/LED Driver B/CS7_B: D197.2, D197.4, D197.6, D198.2, D198.4, D198.6, D199.2, D199.4, D199.6, D200.2, D200.4, D200.6, U6.23 (CS7)
/LED Drivers/LED Driver B/CS8_B: D201.2, D201.4, D201.6, D202.2, D202.4, D202.6, D203.2, D203.4, D203.6, D204.2, D204.4, D204.6, U6.24 (CS8)
/LED Drivers/LED Driver B/CS9_B: D205.2, D205.4, D205.6, D206.2, D206.4, D206.6, D207.2, D207.4, D207.6, D208.2, D208.4, D208.6, U6.25 (CS9)
/LED Drivers/LED Driver B/CS10_B: D209.2, D209.4, D209.6, D210.2, D210.4, D210.6, D211.2, D211.4, D211.6, D212.2, D212.4, D212.6, U6.26 (CS10)
/LED Drivers/LED Driver B/CS11_B: D213.2, D213.4, D213.6, D214.2, D214.4, D214.6, D215.2, D215.4, D215.6, D216.2, D216.4, D216.6, U6.27 (CS11)
/LED Drivers/LED Driver B/CS12_B: D217.2, D217.4, D217.6, D218.2, D218.4, D218.6, D219.2, D219.4, D219.6, D220.2, D220.4, D220.6, U6.28 (CS12)
/LED Drivers/LED Driver B/SW1_B: D176.1, D180.1, D184.1, D188.1, D192.1, D196.1, D200.1, D204.1, D208.1, D212.1, D216.1, D220.1, U6.2 (SW1)
/LED Drivers/LED Driver B/SW2_B: D176.3, D180.3, D184.3, D188.3, D192.3, D196.3, D200.3, D204.3, D208.3, D212.3, D216.3, D220.3, U6.3 (SW2)
/LED Drivers/LED Driver B/SW3_B: D176.5, D180.5, D184.5, D188.5, D192.5, D196.5, D200.5, D204.5, D208.5, D212.5, D216.5, D220.5, U6.4 (SW3)
/LED Drivers/LED Driver B/SW4_B: D175.1, D179.1, D183.1, D187.1, D191.1, D195.1, D199.1, D203.1, D207.1, D211.1, D215.1, D219.1, U6.6 (SW4)
/LED Drivers/LED Driver B/SW5_B: D175.3, D179.3, D183.3, D187.3, D191.3, D195.3, D199.3, D203.3, D207.3, D211.3, D215.3, D219.3, U6.7 (SW5)
/LED Drivers/LED Driver B/SW6_B: D175.5, D179.5, D183.5, D187.5, D191.5, D195.5, D199.5, D203.5, D207.5, D211.5, D215.5, D219.5, U6.8 (SW6)
/LED Drivers/LED Driver B/SW7_B: D174.1, D178.1, D182.1, D186.1, D190.1, D194.1, D198.1, D202.1, D206.1, D210.1, D214.1, D218.1, U6.9 (SW7)
/LED Drivers/LED Driver B/SW8_B: D174.3, D178.3, D182.3, D186.3, D190.3, D194.3, D198.3, D202.3, D206.3, D210.3, D214.3, D218.3, U6.10 (SW8)
/LED Drivers/LED Driver B/SW9_B: D174.5, D178.5, D182.5, D186.5, D190.5, D194.5, D198.5, D202.5, D206.5, D210.5, D214.5, D218.5, U6.11 (SW9)
/LED Drivers/LED Driver B/SW10_B: D173.1, D177.1, D181.1, D185.1, D189.1, D193.1, D197.1, D201.1, D205.1, D209.1, D213.1, D217.1, U6.13 (SW10)
/LED Drivers/LED Driver B/SW11_B: D173.3, D177.3, D181.3, D185.3, D189.3, D193.3, D197.3, D201.3, D205.3, D209.3, D213.3, D217.3, U6.14 (SW11)
/LED Drivers/LED Driver B/SW12_B: D173.5, D177.5, D181.5, D185.5, D189.5, D193.5, D197.5, D201.5, D205.5, D209.5, D213.5, D217.5, U6.15 (SW12)
/LED Drivers/SYNC_OUT: U6.40 (SYNC); also elsewhere on the board
GND: C18.2, C19.2, C20.2, C21.2, C22.2, C23.2, C24.2, C27.2, R18.1, R20.2, U6.5 (PGND), U6.12 (PGND), U6.34 (AGND), U6.44 (ADDR2), U6.48 (GND), U6.49 (GND); also elsewhere on the board
unnamed: R18.2, U6.47 (IICRST)
unnamed: R19.1, U6.46 (~SDB)
unnamed: R20.1, U6.35 (RSET)
VCC: C18.1, C19.1, C20.1, C21.1, C22.1, C23.1, C24.1, U6.20 (PVCC), U6.29 (PVCC), U6.37 (AVCC), U6.38 (DVCC); also elsewhere on the board

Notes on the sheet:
LED_DRIVER_B P29
LED_DRIVER_B P20
LED Driver B - Addr 0x51
LED Driver B - Power Filtering
LED_DRIVER_B PWR_FILTER
LED_DRIVER_B P37/38

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
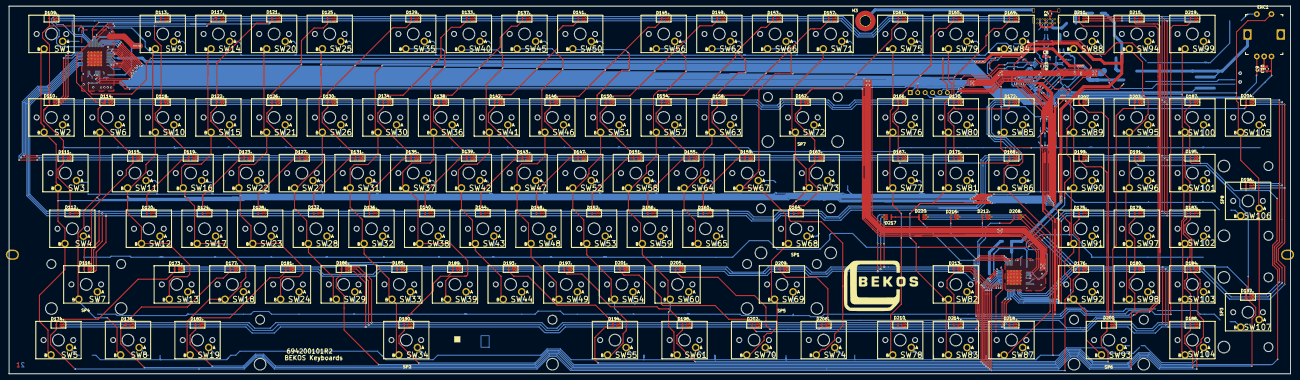
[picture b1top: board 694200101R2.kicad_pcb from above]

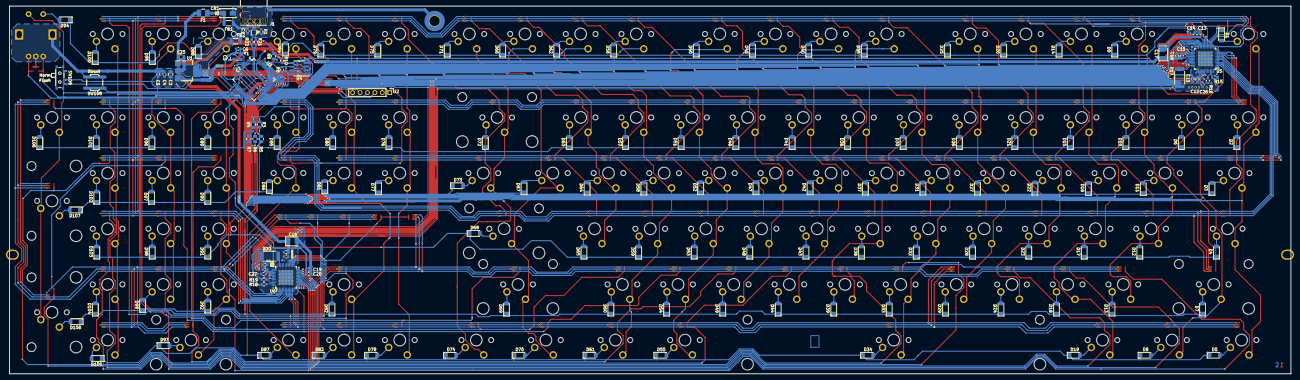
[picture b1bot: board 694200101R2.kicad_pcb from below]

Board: 2 copper layers, 438.6 x 125.8 mm, 400 parts (164 on the bottom side), 227 nets.

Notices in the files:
parts and their libraries:
Copyright 2016 Accelerated Designs. All rights reserved.
